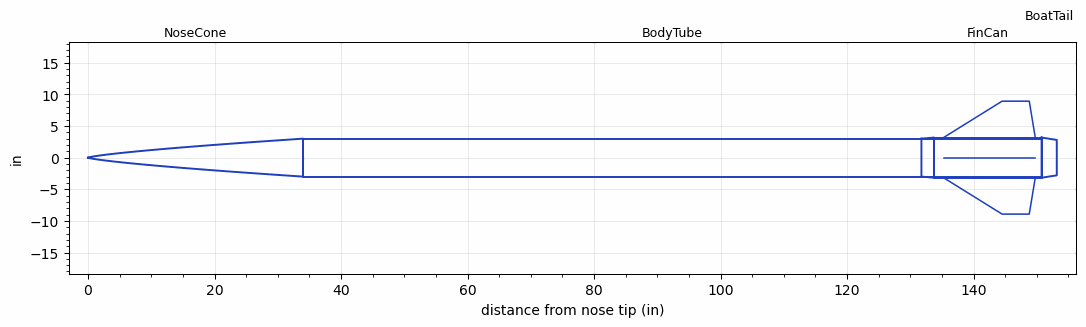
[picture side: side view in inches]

<RASAeroDocument>
 <FileVersion>2</FileVersion>
 <RocketDesign>
  <NoseCone>
   <Length>34</Length>
   <Diameter>6</Diameter>
   <Shape>Power Law</Shape>
   <BluntRadius>0.125</BluntRadius>
   <Location>0</Location>
   <PowerLaw>0.75</PowerLaw>
  </NoseCone>
  <BodyTube>
   <Length>116.75</Length>
   <Diameter>6</Diameter>
   <Location>34</Location>
  </BodyTube>
  <FinCan>
   <Length>17</Length>
   <Diameter>6.35</Diameter>
   <InsideDiameter>6</InsideDiameter>
   <Location>150.75</Location>
   <ShoulderLength>2</ShoulderLength>
   <Offset>-17</Offset>
   <Fin>
    <Count>4</Count>
    <Chord>14.5</Chord>
    <Span>5.75</Span>
    <SweepDistance>9.25</SweepDistance>
    <TipChord>4.3</TipChord>
    <Thickness>0.25</Thickness>
    <LERadius>0.08</LERadius>
    <Location>15.5</Location>
    <AirfoilSection>Hexagonal</AirfoilSection>
    <FX1>0.5</FX1>
    <FX3>0.5</FX3>
   </Fin>
  </FinCan>
  <BoatTail>
   <Length>2.4</Length>
   <Diameter>6.35</Diameter>
   <RearDiameter>5.6</RearDiameter>
   <Location>150.75</Location>
  </BoatTail>
  <Surface>Cast Iron (Very Rough)</Surface>
  <ModifiedBarrowman>False</ModifiedBarrowman>
  <Turbulence>True</Turbulence>
  <UseBooster1>False</UseBooster1>
  <UseBooster2>False</UseBooster2>
 </RocketDesign>
 <LaunchSite>
  <Altitude>3000</Altitude>
  <Pressure>0</Pressure>
  <RodAngle>2</RodAngle>
  <RodLength>18</RodLength>
  <Temperature>85</Temperature>
  <WindSpeed>8</WindSpeed>
 </LaunchSite>
 <Recovery>
  <Altitude1>1000</Altitude1>
  <Altitude2>1000</Altitude2>
  <DeviceType1>None</DeviceType1>
  <DeviceType2>None</DeviceType2>
  <Event1>False</Event1>
  <Event2>False</Event2>
  <Size1>1</Size1>
  <Size2>1</Size2>
  <EventType1>None</EventType1>
  <EventType2>None</EventType2>
  <CD1>1.33</CD1>
  <CD2>1.33</CD2>
 </Recovery>
 <SimulationList>
  <Simulation>
   <SustainerEngine>P9095  (MIT)</SustainerEngine>
   <SustainerLaunchWt>161.1</SustainerLaunchWt>
   <SustainerNozzleDiameter>4.7</SustainerNozzleDiameter>
   <SustainerCG>104</SustainerCG>
   <SustainerIgnitionDelay>0</SustainerIgnitionDelay>
   <Booster1SeparationDelay>0</Booster1SeparationDelay>
   <Booster1IgnitionDelay>0</Booster1IgnitionDelay>
   <IncludeBooster1>False</IncludeBooster1>
   <Booster2Delay>0</Booster2Delay>
   <IncludeBooster2>False</IncludeBooster2>
   <TimetoApogee>68.96632</TimetoApogee>
   <MaxAltitude>85168.38</MaxAltitude>
   <MaxVelocity>3390.692</MaxVelocity>
  </Simulation>
 </SimulationList>
</RASAeroDocument>
